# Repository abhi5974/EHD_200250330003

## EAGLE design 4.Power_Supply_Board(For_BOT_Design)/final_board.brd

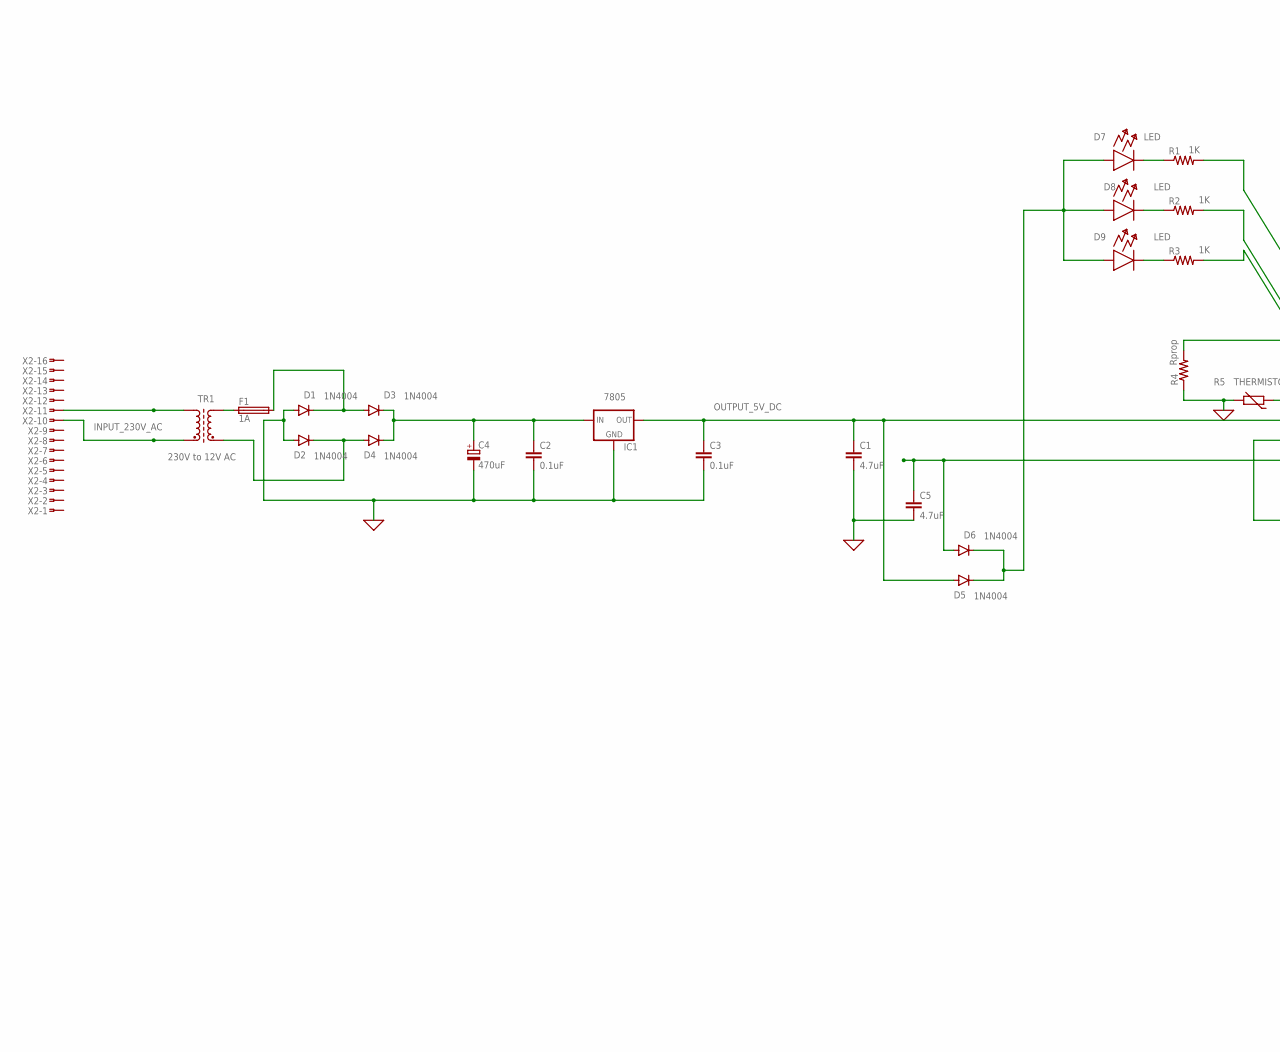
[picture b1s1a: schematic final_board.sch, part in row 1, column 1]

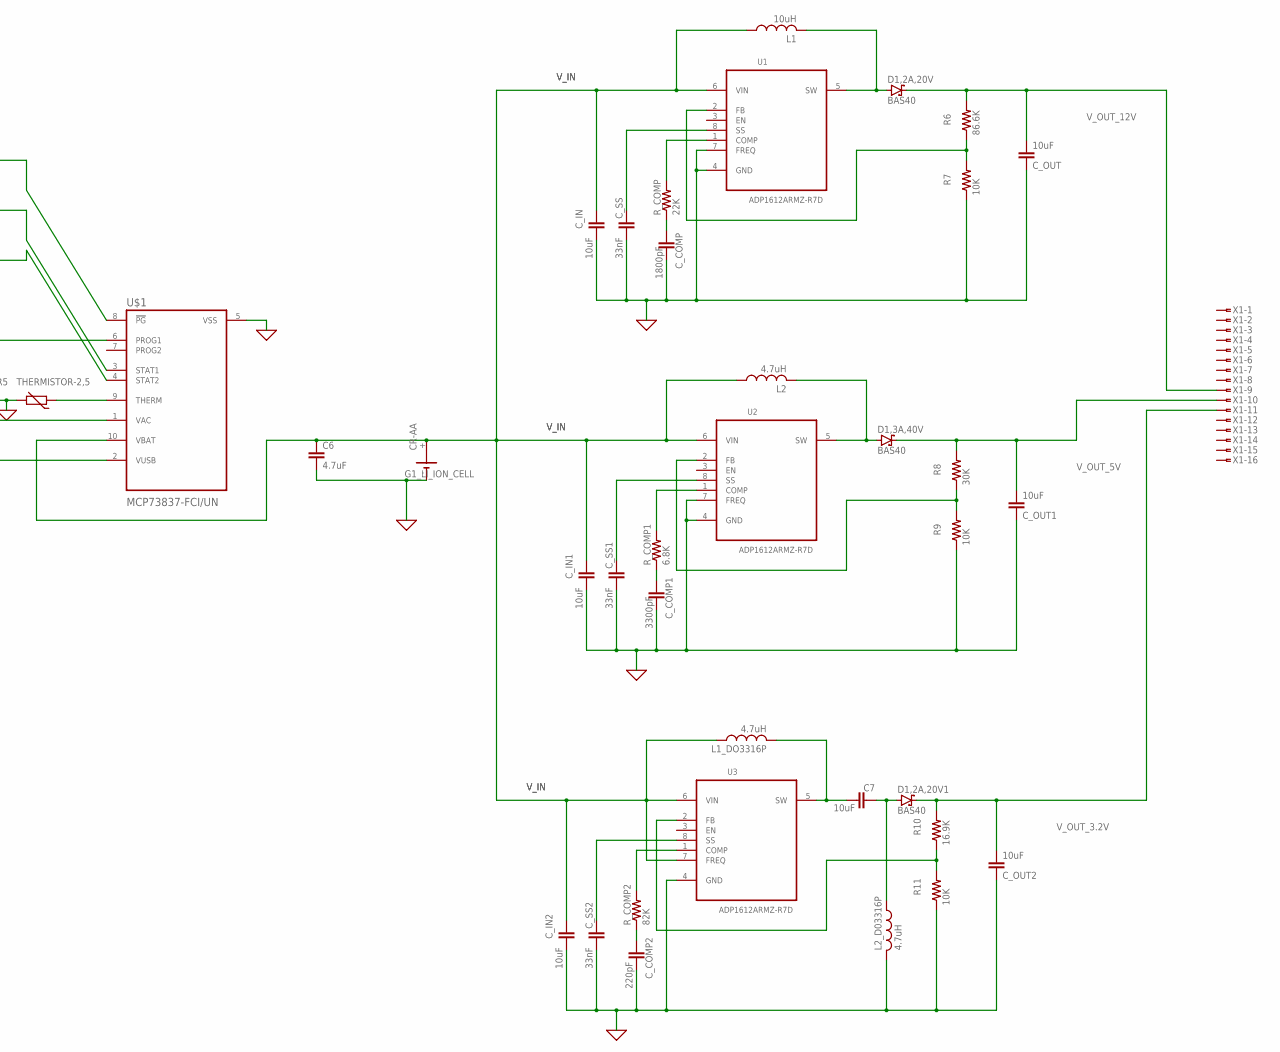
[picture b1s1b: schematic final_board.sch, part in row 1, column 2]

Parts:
C1, C5, C6: 4.7uF; C2.5-3
C2, C3: 0.1uF; C2.5-3
C4: 470uF; 085CS_1AR
C7: 10uF; C2.5-3
C_COMP: 1800pF; C2.5-3
C_COMP1: 3300pF; C2.5-3
C_COMP2: 220pF; C2.5-3
C_IN, C_IN1, C_IN2: 10uF; C2.5-3
C_OUT, C_OUT1, C_OUT2: 10uF; C2.5-3
C_SS, C_SS1, C_SS2: 33nF; C2.5-3
D1, D2, D3, D4, D5, D6: 1N4004; DO41-10
D1,2A,20V, D1,2A,20V1, D1,3A,40V: BAS40; SOT23
F1: 1A; 19559
G1_LI_ION_CELL: CR-AA; CRAA
IC1: 7805; 78XXL
L1: 10uH; 0204/5
L1_DO3316P, L2, L2_D03316P: 4.7uH; 0204/5
R1, R2, R3: 1K; 0204V
R4: Rprop; 0204V
R5: THERMISTOR-2,5; RS-2,5
R6: 86.6K; 0204/7
R7, R9, R11: 10K; 0204/7
R8: 30K; 0204/7
R10: 16.9K; 0204/7
R_COMP: 22K; 0204/7
R_COMP1: 6.8K; 0204/7
R_COMP2: 82K; 0204/7
TR1: 230V to 12V AC; SM-T4
U1, U2, U3: ADP1612ARMZ-R7D; SOIC-08
U$1: MCP73837-FCI/UN; SOP50P490X110-10N
X1, X2: FSIDE-16

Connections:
0: C1.2, C2.2, C3.2, C4.-, C5.2, C6.2, C_COMP.2, C_COMP1.2, C_COMP2.2, C_IN.2, C_IN1.2, C_IN2.2, C_OUT.2, C_OUT1.2, C_OUT2.2, C_SS.2, C_SS1.2, C_SS2.2, D1.A, D2.A, G1_LI_ION_CELL.-, IC1.GND, L2_D03316P.2, R4.1, R5.2, R7.1, R9.1, R11.1, U1.4 (GND), U1.7 (FREQ), U2.4 (GND), U2.7 (FREQ), U3.4 (GND), U$1.5 (VSS)
INPUT_230V_AC: TR1.1 (A1), X2.11
unnamed: TR1.2 (E1), X2.10
unnamed: C5.1, D6.A, U$1.2 (VUSB)
unnamed: D1.C, D3.A, F1.2
unnamed: D2.C, D4.A, TR1.4 (E2)
unnamed: C2.1, C4.+, D3.C, D4.C, IC1.IN
unnamed: F1.1, TR1.5 (A2)
unnamed: R1.2, U$1.8 (!PG)
unnamed: R2.2, U$1.3 (STAT1)
unnamed: R3.2, U$1.4 (STAT2)
unnamed: R5.1, U$1.9 (THERM)
unnamed: R4.2, U$1.6 (PROG1)
unnamed: D5.C, D6.C
unnamed: D1,2A,20V.1 (A), L1.2, U1.5 (SW)
unnamed: C_COMP.1, R_COMP.1
unnamed: R_COMP.2, U1.1 (COMP)
unnamed: C_SS.1, U1.8 (SS)
unnamed: R6.1, R7.2, U1.2 (FB)
unnamed: D1,3A,40V.1 (A), L2.2, U2.5 (SW)
unnamed: C_COMP1.1, R_COMP1.1
unnamed: R_COMP1.2, U2.1 (COMP)
unnamed: C_SS1.1, U2.8 (SS)
unnamed: R8.1, R9.2, U2.2 (FB)
unnamed: C7.1, L1_DO3316P.2, U3.5 (SW)
unnamed: C_COMP2.1, R_COMP2.1
unnamed: R_COMP2.2, U3.1 (COMP)
unnamed: C_SS2.1, U3.8 (SS)
unnamed: R10.1, R11.2, U3.2 (FB)
unnamed: C7.2, D1,2A,20V1.1 (A), L2_D03316P.1
OUTPUT_5V_DC: C1.1, C3.1, D5.A, IC1.OUT, U$1.1 (VAC)
V_IN: C6.1, C_IN.1, C_IN1.1, C_IN2.1, G1_LI_ION_CELL.+, L1.1, L1_DO3316P.1, L2.1, U1.6 (VIN), U2.6 (VIN), U3.6 (VIN), U3.7 (FREQ), U$1.10 (VBAT)
V_OUT_3.2V: C_OUT2.1, D1,2A,20V1.3 (C), R10.2, X1.11
V_OUT_5V: C_OUT1.1, D1,3A,40V.3 (C), R8.2, X1.10
V_OUT_12V: C_OUT.1, D1,2A,20V.3 (C), R6.2, X1.9

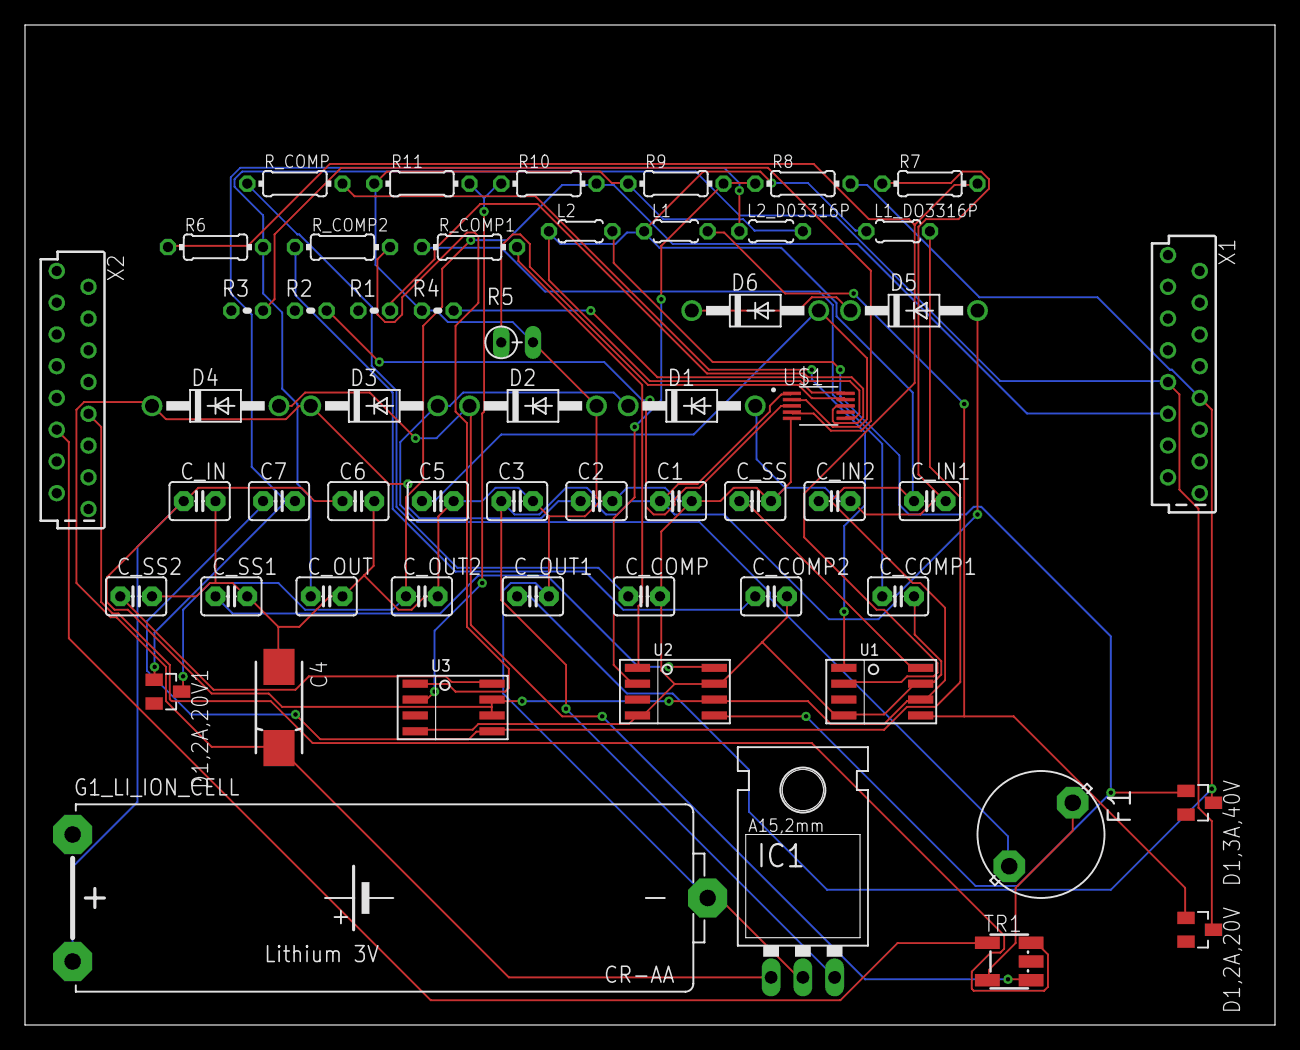
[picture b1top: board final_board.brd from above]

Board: 2 copper layers, 100.0 x 80.0 mm, 56 parts (0 on the bottom side), 35 nets.

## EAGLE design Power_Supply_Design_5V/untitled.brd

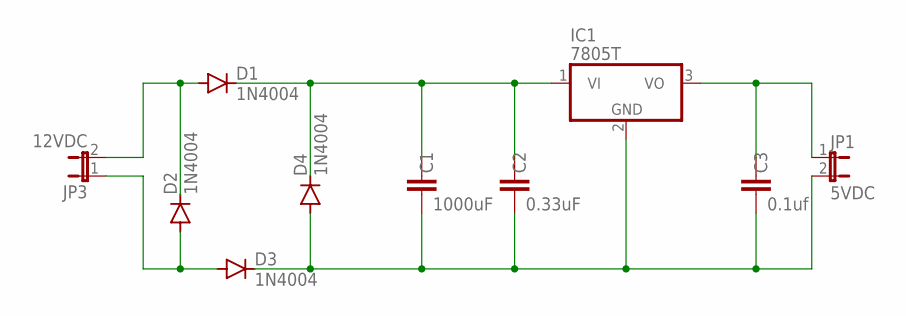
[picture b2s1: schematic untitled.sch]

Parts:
C1: 1000uF; C2.5-3
C2: 0.33uF; C2.5-3
C3: 0.1uf; C2.5-3
D1, D2, D3, D4: 1N4004; DO41-10
IC1: 7805T; TO220H
JP1: 5VDC; JP1
JP3: 12VDC; JP1

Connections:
unnamed: D1.A, D2.C, JP3.2
unnamed: C1.1, C2.1, D1.C, D4.C, IC1.1 (VI)
unnamed: C1.2, C2.2, C3.2, D3.C, D4.A, IC1.2 (GND), JP1.2
unnamed: D2.A, D3.A, JP3.1
unnamed: C3.1, IC1.3 (VO), JP1.1

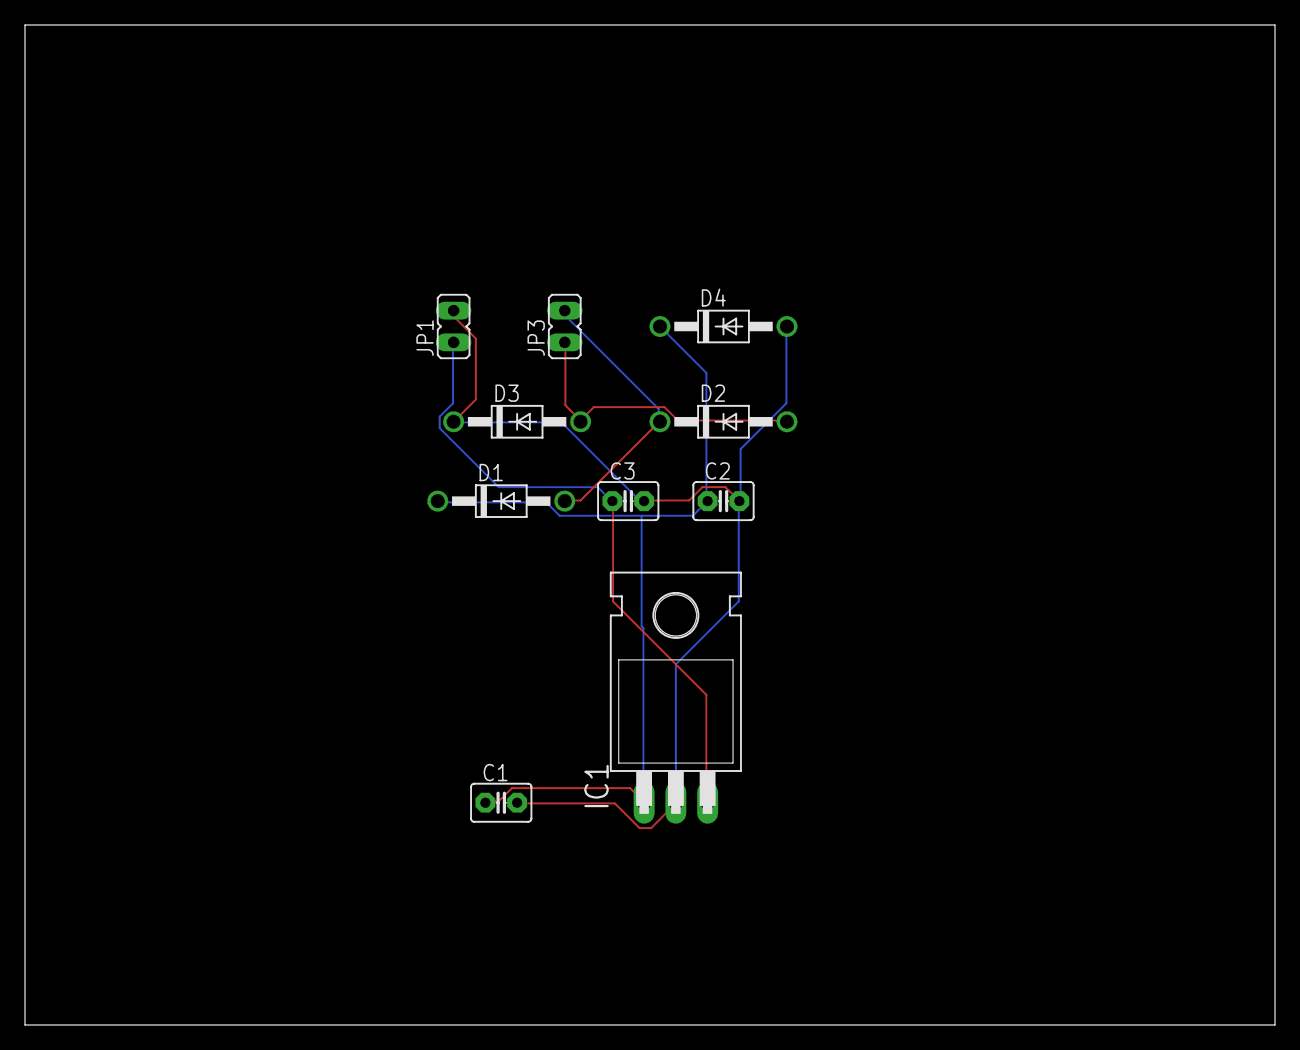
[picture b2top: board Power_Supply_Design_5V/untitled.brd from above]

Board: 2 copper layers, 100.0 x 80.0 mm, 10 parts (0 on the bottom side), 5 nets.

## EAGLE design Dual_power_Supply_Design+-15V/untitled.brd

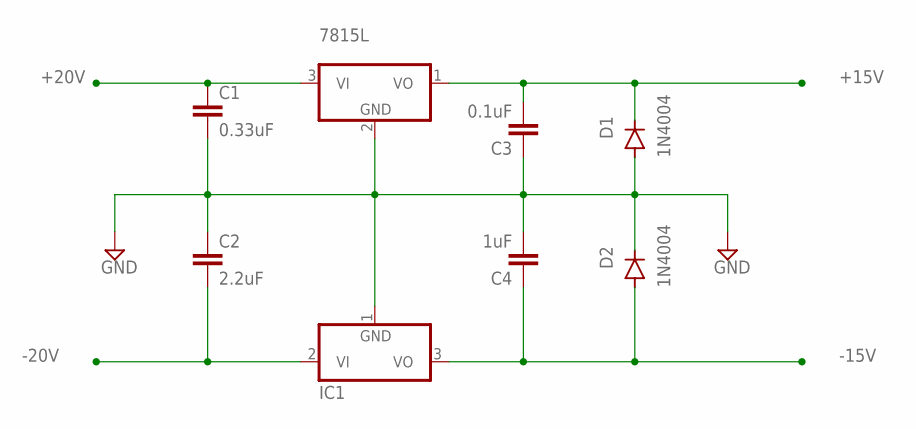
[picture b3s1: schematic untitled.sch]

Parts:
C1: 0.33uF; C2.5-3
C2: 2.2uF; C2.5-3
C3: 0.1uF; C2.5-3
C4: 1uF; C2.5-3
D1, D2: 1N4004; DO41-10
IC1: -15v; TO92
LM7815: 7815L; TO92

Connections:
+15V: C3.2, D1.C, LM7815.1 (VO)
+20V: C1.1, LM7815.3 (VI)
-15V: C4.1, D2.A, IC1.3 (VO)
-20V: C2.2, IC1.2 (VI)
GND: C1.2, C2.1, C3.1, C4.2, D1.A, D2.C, IC1.1 (GND), LM7815.2 (GND)

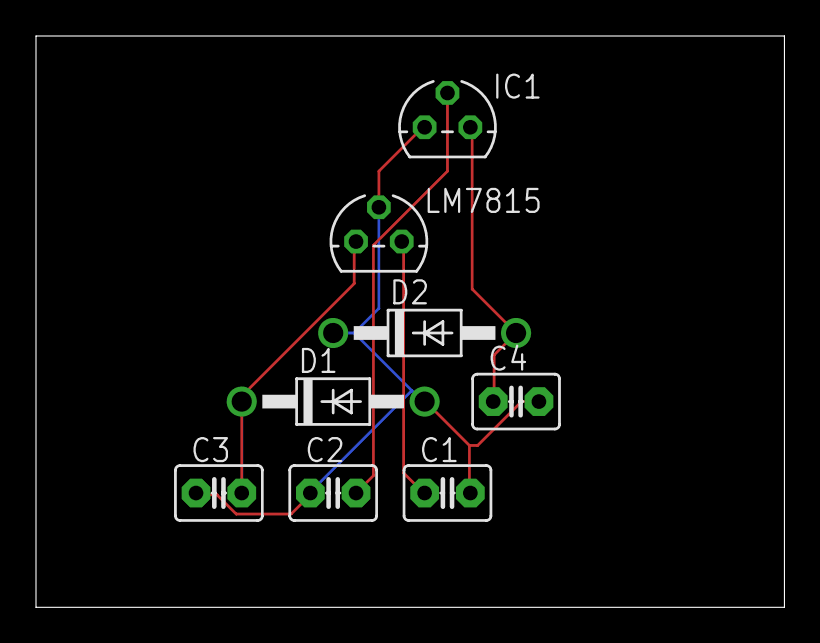
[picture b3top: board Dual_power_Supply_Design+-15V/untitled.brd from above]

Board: 2 copper layers, 41.6 x 31.7 mm, 8 parts (0 on the bottom side), 5 nets.
